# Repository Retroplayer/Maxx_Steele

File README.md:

# Maxx Steele reverse engineering

Firmware and peripheral research for the 1984 Ideal/CBS Toys robot.

- [Pico USB remote emulator: installation and usage](pico/README.md)
- [ROM- and capture-verified remote protocol](docs/remote-protocol.md)
- [Motor COP commands, counters, positions, and stalls](docs/motor-control.md)
- [Cartridge connector pinout, BIGSPACEB, F2, and NMI](docs/cartridge-port.md)
- [I/O register sweep: reads, writes, widths, and decode gaps](docs/io-registers.md)
- [NCR/CBS ASIC pin inventory and unused-port hypothesis](docs/asic-pins.md)
- [RAM ownership, complete zero-page map, and cartridge API constraints](docs/ram-ownership.md)
- [WinCUPL cartridge decoder, pinout, and R/W output](hardware/decoder/README.md)
- [All head messages and proposed 1602 LCD text](docs/head-messages.md)
- [Byte-identical KickAssembler main-ROM source and build](asm/README.md)
- [Memory map](docs/memory-map.md)
- [Head display segment encoding and serial communication](docs/head-display.md)
- [Chest lamps, interfering port writers, and sonar GPIO feasibility](docs/chest-lamps.md)
- [Speech ports, vocabulary, phrases, and expansion research](docs/speech-interface.md)
- [Fixed-layout cartridge format](docs/cartridge-builder-format.md)
- [Original demo cartridge](docs/demo-cartridge.md)

The Pico implementation uses MicroPython PIO for precise waveform generation
and a USB CDC text-command interface. A Windows-compatible Python console is
provided in `pc/remote_cli.py`. Host tests validate generated waveforms against
the original robot ROM. Physical Pico operation and the transmitter-jack
electrical interface still require measurement and testing.

Original uploaded ROM images and captures are kept outside the checkout in
the workspace attachments; the tools accept their paths and verify the mapped
ROM's hash. No cartridge template has been modified.

A complete ZIP containing the source, documentation, and verified ROM image
is available at [dist/Maxx_Steele_project.zip](dist/Maxx_Steele_project.zip).

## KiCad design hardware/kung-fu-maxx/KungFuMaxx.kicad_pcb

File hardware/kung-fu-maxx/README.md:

# Kung Fu Maxx — KiCad conversion, revision A0

A Maxx Steele cartridge PCB derived from Kim Jørgensen's original
STM32F405-based **Kung Fu Flash**. This is an edited schematic and routed-PCB
prototype, not a tested cartridge or a firmware release.

**A0 uses four copper layers:** F.Cu, In1.Cu ground plane, In2.Cu bus
crossovers with ground fill, and B.Cu. Board thickness is 1.6 mm; the final
fabricator stackup remains to be specified.

Open **KungFuMaxx.kicad_pro** in **KiCad 9**. The schematic, board, symbols, and
footprints are supplied locally; no custom libraries need downloading.

## Changes from Kung Fu Flash

- Replaced the C64 edge connector with **44 uniquely numbered Maxx contacts**.
- Connected all 16 address lines to STM32 PB0–PB15, retaining the fast port layout.
- Connected D0–D7 through the original eight 100-ohm series resistors to PC0–PC7.
- Connected **J400 pin 12 WRB to PA0** and **pin 14 OEB to PA8**.
- Connected switched **5 V at pin 41** to the regulator; ground is pins 1 and 43.
- Left battery voltage **pin 39 isolated**, along with the speech bus and other
  unresolved expansion signals. The tentative NMI pin is also disconnected in A0.
- Removed the C64 host-reset driver Q1/R3/R4 and disconnected C64-only controls.
- Retained the MCU support circuitry, USB, SDIO/microSD, programming header,
  regulator, three buttons, and LED at their original positions.
- Rerouted the host bus; retained original fine-pitch escape routing where useful.
- Added two inner layers to finish address-bus crossovers while preserving the
  existing outer-layer circuitry.
- Corrected the original SD footprint courtyard and off-board silkscreen.
- Extended the upper USB-side outline **1.375 mm** to clear its mounting-pad
  copper. The cartridge tongue, 2.54 mm pitch, and original 1.6 mm thickness remain.
- Added A0 prototype markings and retained upstream attribution/license.

The original source files are preserved unchanged in `upstream/`, including
its XML netlist. Original project: https://github.com/KimJorgensen/KungFuFlash
at commit `7121a018c8608feafc2180d910ce58acddbec5e3`. Development moved to
https://codeberg.org/KimJorgensen/KungFuFlash . This is an altered derivative,
not a release by the Kung Fu Flash author. See `LICENSE.upstream`.

## Connector orientation — review before fabrication

The new footprint uses **even contacts 2–44 left-to-right on F.Cu**, viewed from
the component side with the fingers pointing down. The corresponding B.Cu
positions are odd contacts 1–43; viewing the back directly mirrors their order.
See `PINOUT.md` and `pin-map.json`.

This is an explicit physical convention, not a verified insertion drawing.
Confirm it against the actual Maxx slot and the owner's outside-looking-in
connector drawing before ordering boards. The two ground contacts alone do not
prove end-for-end orientation. Do not use ordinary C64 signal numbering.

The owner's v2 connector PDF swaps WRB/OEB. **Use the owner's later correction:
12=WRB and 14=OEB**, as implemented here.

## Electrical and firmware limits

The hardware follows KFF's direct STM32 bus approach, with **3.3 V output-high
levels** and no dedicated level-translator ICs. The 100-ohm resistors are not
level translators. Verify the exact STM32's pin tolerance and Maxx's data-input
thresholds, including power sequencing. Do not apply this wiring directly to
the RP2350 board; it is a different MCU/interface.

WRB is the owner-confirmed RAM write strobe. OEB's timing, data-valid intervals,
and bus release requirements still need measurement. F2, WEB, BIGSPACEB, and
RESET SYSB are deliberately not used to guess a CPU-phase or select signal.

**A Maxx-specific STM32 firmware port is still required. Do not install the
stock C64 KFF firmware as a Maxx implementation.** The stock C64 launcher and
PHI2-synchronized handler are incompatible. This PCB conversion does not itself
provide RAM/ROM emulation. The proposed first firmware test serves a small
cartridge ROM at $A000, followed by RAM and USB/SD mailbox services.

Power is from **VSW**, so the board and its volatile emulated RAM lose power
when that rail switches off. Retention requires a separate solution. The Maxx
CPU/RAM can remain powered during sleep while VSW is off: powered-off STM32
pin behavior and possible back-powering must be checked before connection. Leave
**J1 open** when robot-powered: it directly joins USB VBUS to the cartridge
5 V rail when fitted, rather than providing automatic power-source isolation.

## Checks and previews

The current machine-readable results are in `reports/`; `CHECKS.md` records
what passed and what remains unverified. No rule violations are hidden with
DRC exclusions. The one explicit custom rule permits the plated edge fingers
of U1 to approach the routed board edge; ordinary copper retains edge clearance.

- `previews/KungFuMaxx-schematic.pdf`: schematic.
- `previews/`: front/back layout and unpopulated-board previews.
- `reports/schematic-netlist.xml`: netlist exported from the native schematic.
- `reports/connectivity-verification.json`: independent core/pinout checks.
- `upstream/`: the unchanged design used as a reference.

To repeat the checks on Linux with KiCad 9 and its pcbnew Python module:

```sh
tools/kicad.sh sch export netlist --format kicadxml \
  -o reports/schematic-netlist.xml KungFuMaxx.kicad_sch
tools/kicad.sh sch erc --format json --exit-code-violations \
  -o reports/erc.json KungFuMaxx.kicad_sch
tools/kicad.sh pcb drc --format json --schematic-parity --exit-code-violations \
  -o reports/drc.json KungFuMaxx.kicad_pcb
/usr/bin/python3 tools/verify_design.py
```

KiCad's own GUI ERC/DRC dialogs provide the corresponding checks on Windows.
A clean CAD check establishes connectivity/clearance under the stated rules;
it does not establish ASIC voltage margins, bus timing, physical fit, or firmware
operation. Edge finish/bevel and manufacturing details need review with the PCB
supplier after the connector orientation has been confirmed.

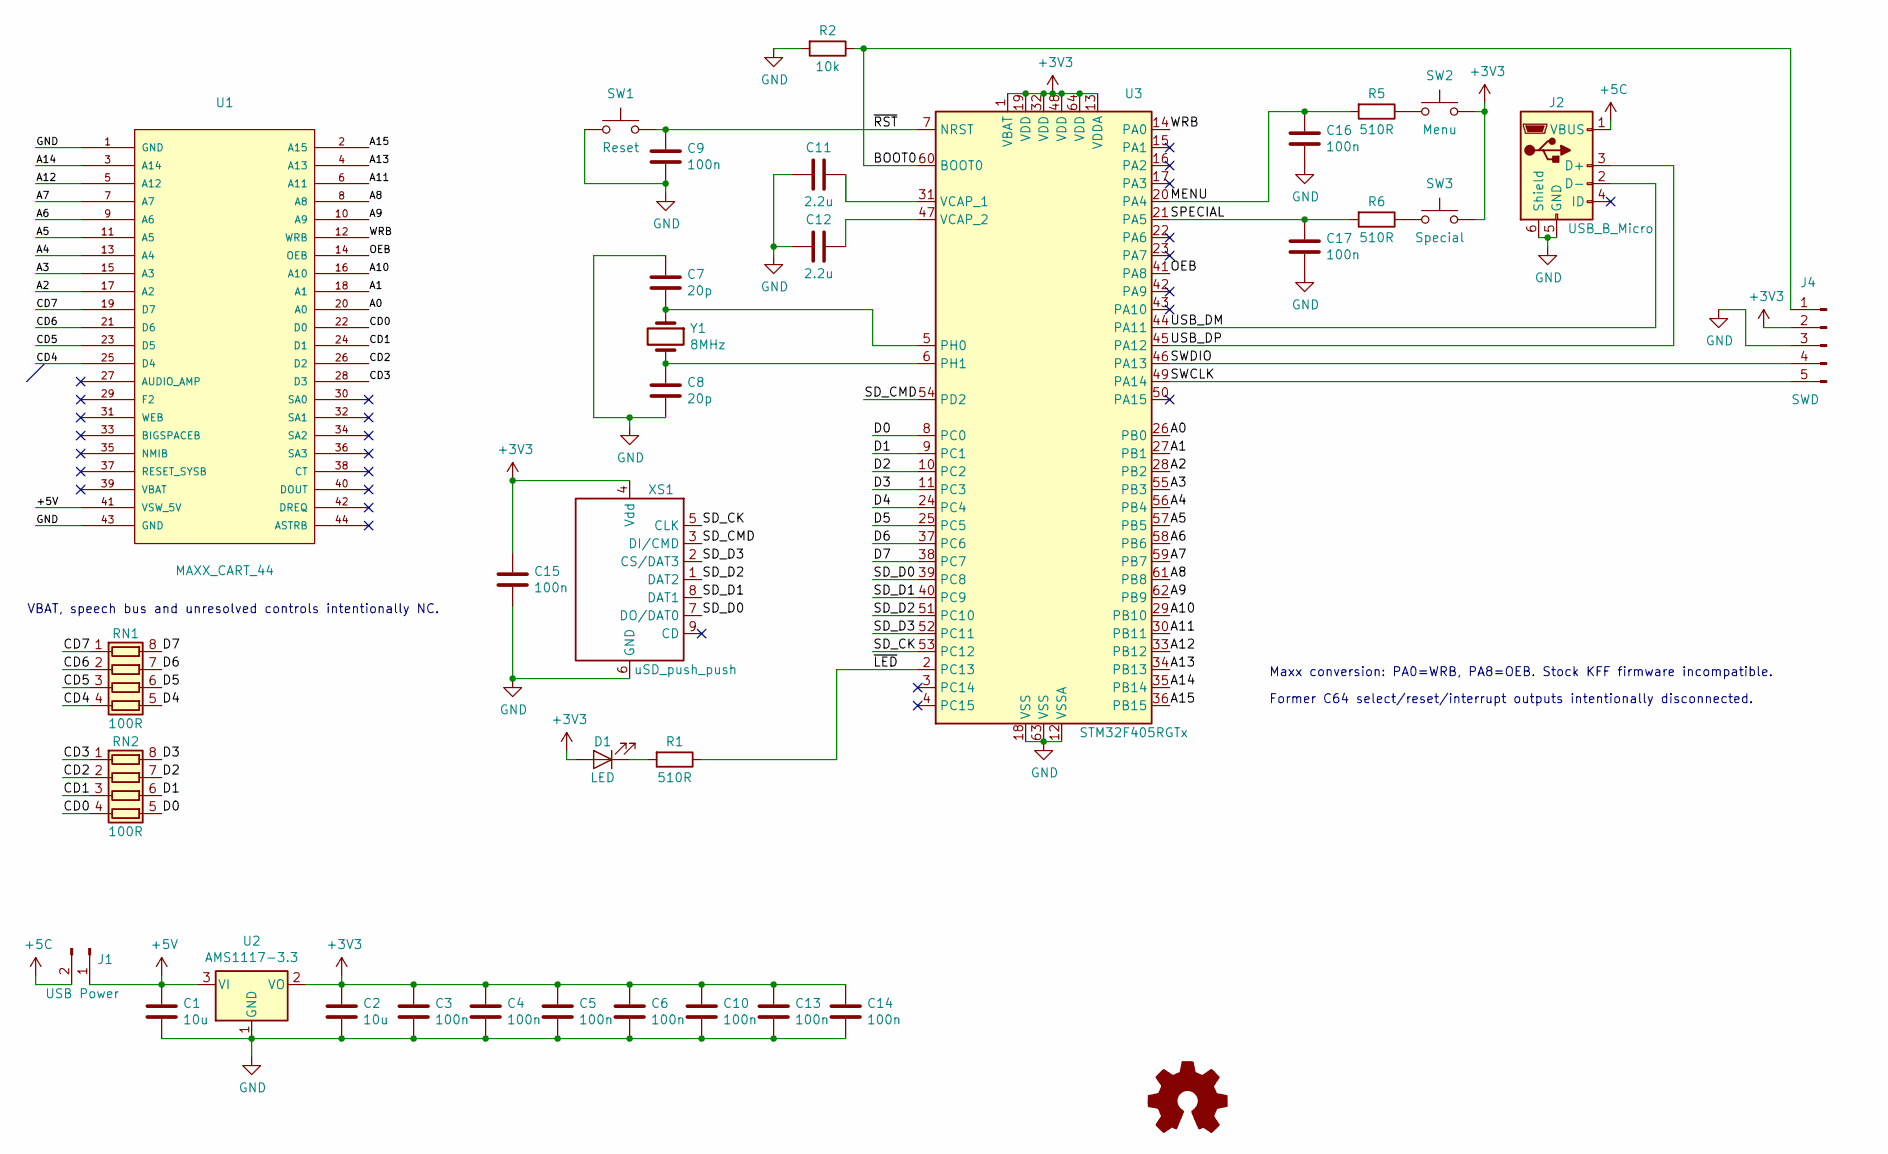
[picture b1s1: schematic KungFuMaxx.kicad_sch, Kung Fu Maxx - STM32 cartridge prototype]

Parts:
C1, C2: 10u; C_0805_2012Metric_Pad1.15x1.40mm_HandSolder
C3, C4, C5, C6, C9, C10, C13, C14, C15, C16, C17: 100n; C_0603_1608Metric_Pad1.05x0.95mm_HandSolder
C7, C8: 20p; C_0603_1608Metric_Pad1.05x0.95mm_HandSolder
C11, C12: 2.2u; C_0805_2012Metric_Pad1.15x1.40mm_HandSolder
D1: LED; LED_0805_2012Metric_Pad1.15x1.40mm_HandSolder
J1: USB Power; PinHeader_1x02_P2.54mm_Vertical
J2: USB_B_Micro; Conn_USBmicro-B_ebay-side_TH
J4: SWD; PinHeader_1x05_P2.54mm_Vertical
R1, R5, R6: 510R; R_0805_2012Metric_Pad1.15x1.40mm_HandSolder
R2: 10k; R_0805_2012Metric_Pad1.15x1.40mm_HandSolder
RN1, RN2: 100R; R_Array_Convex_4x0603
SW1: Reset; SW_PUSH_6mm_H8mm
SW2: Menu; SW_PUSH_6mm_H8mm
SW3: Special; SW_PUSH_6mm_H8mm
U1: MAXX_CART_44; Maxx_Edge44
U2: AMS1117-3.3; SOT-223-3_TabPin2
U3: STM32F405RGTx; LQFP-64_10x10mm_P0.5mm
XS1: uSD_push_push; Conn_uSDcard
Y1: 8MHz; Crystal_SMD_5032-2Pin_5.0x3.2mm

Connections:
+3V3: C2.1, C3.1, C4.1, C5.1, C6.1, C10.1, C13.1, C14.1, C15.1, D1.2 (A), J4.2, SW2.1, SW3.1, U2.2 (VO), U3.1 (VBAT), U3.13 (VDDA), U3.19 (VDD), U3.32 (VDD), U3.48 (VDD), U3.64 (VDD), XS1.4 (Vdd)
+5C: J1.2, J2.1 (VBUS)
+5V: C1.1, J1.1, U1.41 (VSW_5V), U2.3 (VI)
/A0: U1.20 (A0), U3.26 (PB0)
/A1: U1.18 (A1), U3.27 (PB1)
/A2: U1.17 (A2), U3.28 (PB2)
/A3: U1.15 (A3), U3.55 (PB3)
/A4: U1.13 (A4), U3.56 (PB4)
/A5: U1.11 (A5), U3.57 (PB5)
/A6: U1.9 (A6), U3.58 (PB6)
/A7: U1.7 (A7), U3.59 (PB7)
/A8: U1.8 (A8), U3.61 (PB8)
/A9: U1.10 (A9), U3.62 (PB9)
/A10: U1.16 (A10), U3.29 (PB10)
/A11: U1.6 (A11), U3.30 (PB11)
/A12: U1.5 (A12), U3.33 (PB12)
/A13: U1.4 (A13), U3.34 (PB13)
/A14: U1.3 (A14), U3.35 (PB14)
/A15: U1.2 (A15), U3.36 (PB15)
/BOOT0: J4.1, R2.1, U3.60 (BOOT0)
/CD0: RN2.4 (R4.1), U1.22 (D0)
/CD1: RN2.3 (R3.1), U1.24 (D1)
/CD2: RN2.2 (R2.1), U1.26 (D2)
/CD3: RN2.1 (R1.1), U1.28 (D3)
/CD4: RN1.4 (R4.1), U1.25 (D4)
/CD5: RN1.3 (R3.1), U1.23 (D5)
/CD6: RN1.2 (R2.1), U1.21 (D6)
/CD7: RN1.1 (R1.1), U1.19 (D7)
/D0: RN2.5 (R4.2), U3.8 (PC0)
/D1: RN2.6 (R3.2), U3.9 (PC1)
/D2: RN2.7 (R2.2), U3.10 (PC2)
/D3: RN2.8 (R1.2), U3.11 (PC3)
/D4: RN1.5 (R4.2), U3.24 (PC4)
/D5: RN1.6 (R3.2), U3.25 (PC5)
/D6: RN1.7 (R2.2), U3.37 (PC6)
/D7: RN1.8 (R1.2), U3.38 (PC7)
/MENU: C16.1, R5.2, U3.20 (PA4)
/OEB: U1.14 (OEB), U3.41 (PA8)
/SD_CK: U3.53 (PC12), XS1.5 (CLK)
/SD_CMD: U3.54 (PD2), XS1.3 (DI/CMD)
/SD_D0: U3.39 (PC8), XS1.7 (DO/DAT0)
/SD_D1: U3.40 (PC9), XS1.8 (DAT1)
/SD_D2: U3.51 (PC10), XS1.1 (DAT2)
/SD_D3: U3.52 (PC11), XS1.2 (CS/DAT3)
/SPECIAL: C17.1, R6.2, U3.21 (PA5)
/SWCLK: J4.5, U3.49 (PA14)
/SWDIO: J4.4, U3.46 (PA13)
/USB_DM: J2.2 (D-), U3.44 (PA11)
/USB_DP: J2.3 (D+), U3.45 (PA12)
/WRB: U1.12 (WRB), U3.14 (PA0)
/~LED: R1.1, U3.2 (PC13)
/~RST: C9.1, SW1.2, U3.7 (NRST)
GND: C1.2, C2.2, C3.2, C4.2, C5.2, C6.2, C7.1, C8.2, C9.2, C10.2, C11.1, C12.2, C13.2, C14.2, C15.2, C16.2, C17.2, J2.5 (GND), J2.6 (Shield), J4.3, R2.2, SW1.1, U1.1 (GND), U1.43 (GND), U2.1 (GND), U3.12 (VSSA), U3.18 (VSS), U3.63 (VSS), XS1.6 (GND)
unnamed: D1.1 (K), R1.2
unnamed: R5.1, SW2.2
unnamed: R6.1, SW3.2
unnamed: C7.2, U3.5 (PH0), Y1.1
unnamed: C8.1, U3.6 (PH1), Y1.2
unnamed: C11.2, U3.31 (VCAP_1)
unnamed: C12.1, U3.47 (VCAP_2)

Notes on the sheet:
Former C64 select/reset/interrupt outputs intentionally disconnected.
Maxx conversion: PA0=WRB, PA8=OEB. Stock KFF firmware incompatible.
VBAT, speech bus and unresolved controls intentionally NC.

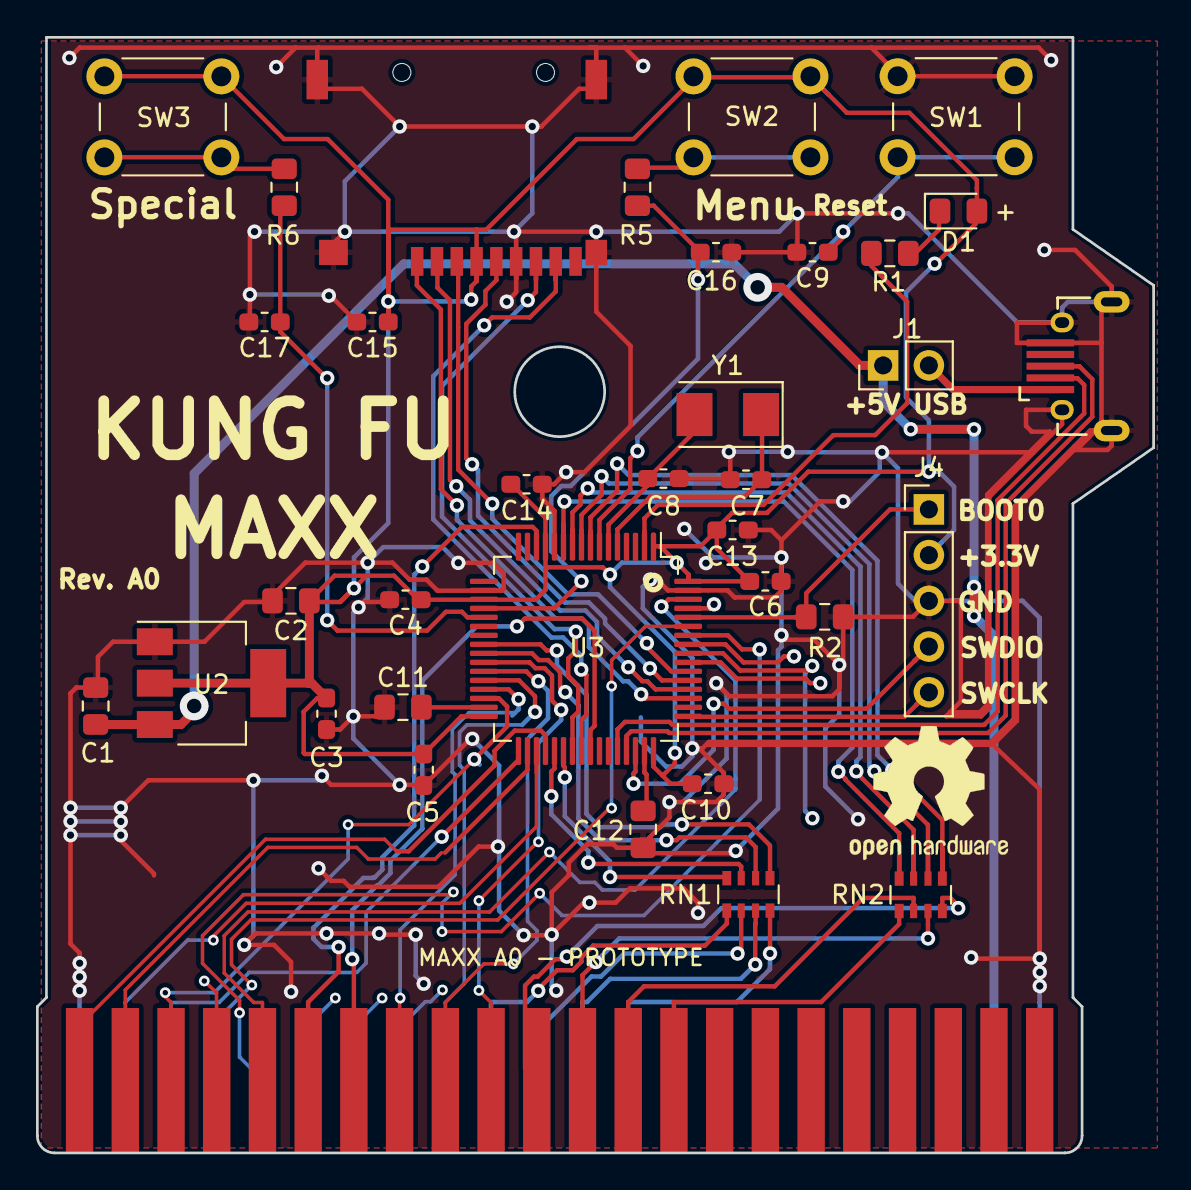
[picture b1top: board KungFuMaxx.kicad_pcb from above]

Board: 4 copper layers, 62.0 x 62.0 mm, 35 parts (0 on the bottom side), 60 nets.

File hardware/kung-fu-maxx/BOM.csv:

Reference,Value,Footprint,Note
C1,10u,MaxxKFF:C_0805_2012Metric_Pad1.15x1.40mm_HandSolder,
C2,10u,MaxxKFF:C_0805_2012Metric_Pad1.15x1.40mm_HandSolder,
C3,100n,MaxxKFF:C_0603_1608Metric_Pad1.05x0.95mm_HandSolder,
C4,100n,MaxxKFF:C_0603_1608Metric_Pad1.05x0.95mm_HandSolder,
C5,100n,MaxxKFF:C_0603_1608Metric_Pad1.05x0.95mm_HandSolder,
C6,100n,MaxxKFF:C_0603_1608Metric_Pad1.05x0.95mm_HandSolder,
C7,20p,MaxxKFF:C_0603_1608Metric_Pad1.05x0.95mm_HandSolder,
C8,20p,MaxxKFF:C_0603_1608Metric_Pad1.05x0.95mm_HandSolder,
C9,100n,MaxxKFF:C_0603_1608Metric_Pad1.05x0.95mm_HandSolder,
C10,100n,MaxxKFF:C_0603_1608Metric_Pad1.05x0.95mm_HandSolder,
C11,2.2u,MaxxKFF:C_0805_2012Metric_Pad1.15x1.40mm_HandSolder,
C12,2.2u,MaxxKFF:C_0805_2012Metric_Pad1.15x1.40mm_HandSolder,
C13,100n,MaxxKFF:C_0603_1608Metric_Pad1.05x0.95mm_HandSolder,
C14,100n,MaxxKFF:C_0603_1608Metric_Pad1.05x0.95mm_HandSolder,
C15,100n,MaxxKFF:C_0603_1608Metric_Pad1.05x0.95mm_HandSolder,
C16,100n,MaxxKFF:C_0603_1608Metric_Pad1.05x0.95mm_HandSolder,
C17,100n,MaxxKFF:C_0603_1608Metric_Pad1.05x0.95mm_HandSolder,
D1,LED,MaxxKFF:LED_0805_2012Metric_Pad1.15x1.40mm_HandSolder,
J1,USB Power,MaxxKFF:PinHeader_1x02_P2.54mm_Vertical,
J2,USB_B_Micro,MaxxKFF:Conn_USBmicro-B_ebay-side_TH,
J4,SWD,MaxxKFF:PinHeader_1x05_P2.54mm_Vertical,
R1,510R,MaxxKFF:R_0805_2012Metric_Pad1.15x1.40mm_HandSolder,
R2,10k,MaxxKFF:R_0805_2012Metric_Pad1.15x1.40mm_HandSolder,
R5,510R,MaxxKFF:R_0805_2012Metric_Pad1.15x1.40mm_HandSolder,
R6,510R,MaxxKFF:R_0805_2012Metric_Pad1.15x1.40mm_HandSolder,
RN1,100R,MaxxKFF:R_Array_Convex_4x0603,
RN2,100R,MaxxKFF:R_Array_Convex_4x0603,
SW1,Reset,MaxxKFF:SW_PUSH_6mm_H8mm,
SW2,Menu,MaxxKFF:SW_PUSH_6mm_H8mm,
SW3,Special,MaxxKFF:SW_PUSH_6mm_H8mm,
U1,MAXX_CART_44,MaxxKFF:Maxx_Edge44,Integral PCB contacts; not a purchased component
U2,AMS1117-3.3,MaxxKFF:SOT-223-3_TabPin2,
U3,STM32F405RGTx,MaxxKFF:LQFP-64_10x10mm_P0.5mm,
XS1,uSD_push_push,MaxxKFF:Conn_uSDcard,
Y1,8MHz,MaxxKFF:Crystal_SMD_5032-2Pin_5.0x3.2mm,

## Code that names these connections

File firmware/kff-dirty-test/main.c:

/* Maxx / original STM32F405 KFF bench experiment. Standalone firmware. */
#include <stdint.h>
#define REG(a) (*(volatile uint32_t *)(a))
#define RCC 0x40023800u
#define GPIOA 0x40020000u
#define GPIOB 0x40020400u
#define GPIOC 0x40020800u
#define IDR 0x10u
#define WRB (1u << 0)
#define OEB (1u << 8)
#define DATA_MODE (*(volatile uint16_t *)GPIOC)
#define DATA_OUT (*(volatile uint8_t *)(GPIOC + 0x14))
extern uint32_t _sidata, _sdata, _edata, _sbss, _ebss;
extern uint32_t _siram, _sram, _eram;
static uint8_t image[8192] __attribute__((aligned(4)));
#include "image.h"
static void clocks(void) {
    REG(RCC+0x40) |= 1u<<28; (void)REG(RCC+0x40); /* PWR clock */
    REG(0x40007000) |= 1u<<14; /* voltage scale 1 */
    REG(RCC) |= 1u<<16; /* original KFF 8MHz crystal */
    while (!(REG(RCC)&(1u<<17))) {} /* Fail with bus still input. */
    REG(RCC+8) = (5u<<10)|(4u<<13); /* APB1 /4, APB2 /2 */
    REG(RCC+4) = 8u|(336u<<6)|(1u<<22)|(7u<<24); /* PLL 168MHz */
    REG(0x40023c00) = 5u|(7u<<8); /* flash 5WS, prefetch and caches */
    REG(RCC) |= 1u<<24;
    while (!(REG(RCC)&(1u<<25))) {}
    REG(RCC+8) |= 2u;
    while ((REG(RCC+8)&12u)!=8u) {}
}
/* SRAM-resident loop. No interrupts, flash writes, USB or SD activity.
 * Assumes OEB low + WRB high qualifies a read with stable address.
 * Release on strobe end, write or address change. Requires timing validation.
 */
__attribute__((section(".ramcode"),noreturn,noinline))
static void serve(void) {
    for (;;) {
        uint32_t control=REG(GPIOA+IDR);
        if ((control&(OEB|WRB))!=WRB) continue;
        uint32_t address=REG(GPIOB+IDR)&0xffffu;
        if ((address&0xe000u)!=0xa000u) continue;
        uint32_t value=image[address&0x1fffu];
        DATA_OUT=value; /* preload before changing direction */
        if ((REG(GPIOA+IDR)&(OEB|WRB))!=WRB ||
            (REG(GPIOB+IDR)&0xffffu)!=address) continue;
        DATA_MODE=0x5555u;
        while ((REG(GPIOA+IDR)&(OEB|WRB))==WRB &&
               (REG(GPIOB+IDR)&0xffffu)==address) {}
        DATA_MODE=0;
    }
}
void Reset_Handler(void) {
    __asm volatile("cpsid i");
    uint32_t *s=&_sidata;
    for(uint32_t *d=&_sdata;d<&_edata;) *d++=*s++;
    s=&_siram;
    for(uint32_t *d=&_sram;d<&_eram;) *d++=*s++;
    for(uint32_t *d=&_sbss;d<&_ebss;) *d++=0;
    REG(RCC+0x30)|=7u; (void)REG(RCC+0x30);
    REG(GPIOB)=0; REG(GPIOB+0x0c)=0;
    DATA_MODE=0; REG(GPIOC+0x0c)&=~0xffffu;
    /* PC12 reset driver, PC14/15 and other C64 controls remain inputs.
       Keep PA13/14 SWD. External harness pull-ups on PA0 and PA8. */
    REG(GPIOA)&=~((3u<<0)|(3u<<16));
    REG(GPIOA+0x0c)&=~((3u<<0)|(3u<<16));
    REG(GPIOC+8)|=0xffffu; /* very high speed PC0..7 */
    clocks();
    for(uint32_t i=0;i<sizeof image;i++) image[i]=boot_image[i];
    REG(GPIOC+0x18)=1u<<(13+16); /* LED active low */
    REG(GPIOC)=(REG(GPIOC)&~(3u<<26))|(1u<<26);
    __asm volatile("dsb\n isb" ::: "memory");
    serve();
}
void Fault_Handler(void) {
    DATA_MODE=0;
    for(;;) {}
}
